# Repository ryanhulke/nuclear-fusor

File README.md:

# Nuclear Fusor
A [nuclear fusor](https://en.wikipedia.org/wiki/Fusor) is an inertial electrostatic confinement device that uses a strong electric field to ionize deuterium gas and accelerate the ions toward the center of a vacuum chamber. This is accomplished by applying a large negative voltage to an inner metal grid (the cathode) relative to the grounded chamber wall (the anode). The chamber is operated at low pressure so that ions can travel significant distances and gain energy from the electric field before colliding with other particles. Near the center of the device, some ions collide with enough kinetic energy that, although they still cannot classically overcome the strong [Coulomb repulsion force](https://en.wikipedia.org/wiki/Coulomb's_law) between their positively charged nuclei, they can occasionally [tunnel](https://en.wikipedia.org/wiki/Quantum_tunnelling) through the Coulomb barrier and may fuse, releasing energy and producing fusion products such as neutrons. These devices are purely experimental; they are highly energy-inefficient and have no commercial future. If you have to ask, "then why would I build one?", you probably shouldn't.

## Project Description
Hardware, firmware, and desktop software for the fusor. The build employs 3 microcontrollers with Bluetooth Low-Energy (BLE). One interfaces with the pressure gauge and streams pressure readings to the control panel, another monitors the high-voltage and current, and the third actuates the gas metering valve for remote pressure control. The desktop app control panel brings the live readouts and valve controls together, with option to stream your phone camera to your computer so you can view the plasma at a safe distance. You can also replay recorded sensor logs and camera footage in the control panel for post-run analysis, in either standard or mobile view.

## Core Components
- a vacuum pump
  - https://www.amazon.com/Kozyvacu-Dual-Stage-HVAC-Vacuum-Pump/dp/B01N0SYCL4/ref=sr_1_1?sr=8-1
- a vacuum chamber with a view port
  - source these parts from ebay. Use KF or Conflat fittings.
- a high-voltage feedthrough into the chamber
- an inner grid connected to the feedthrough (ex. protein shaker ball)
- a variable power supply capable of at least -20kV at a few mA
- deuterium gas source (or just air for testing)
- MKS 901P pressure gauge
- pressure gauge readout board ([pressure-gauge-readout\hardware](pressure-gauge-readout/hardware))
-  remote-controlled valve ([valve-control/Parts.md](valve-control/Parts.md))
- ammeter/voltmeter readout board ([meter-readouts\hardware](meter-readouts/hardware))
- NEMA 17 Stepper motor (mounted to a needle valve on the deuterium inlet side) and driver
- (optional) ESP32-C6 microcontroller to control the motor
  - a more efficient design would be to incorporate valve control into the meter readout board's PCB

## Repository Layout

| Path | Purpose |
| --- | --- |
| `control-panel/` | Windows OpenGL control panel for pressure, meter, valve control, sensor logging, camera background, and playback. |
| `meter-readouts/` | ESP32-C6 firmware and KiCad hardware for the high-voltage/current readout board. |
| `pressure-gauge-readout/` | ESP32-S3 firmware, desktop utilities, and KiCad hardware for the MKS 901P pressure gauge BLE bridge. |
| `valve-control/` | ESP32-C6 firmware for the stepper-driven valve controller. |
| `docs/` | Project notes and supporting documentation. |

Generated build outputs, local logs, camera media, reference papers, IDE state, and local tool installs are intentionally ignored.

## Getting Started
First, check out the hardware and parts lists to make sure you have what you need. Then, set up the software toolchain(s) for the components you want to build.

| What | Toolchain | Where to start |
| --- | --- | --- |
| **Control panel** — the Windows desktop app | CMake + Visual Studio C++ build tools + OpenCV | [control-panel/README.md](control-panel/README.md) |
| **Firmware** — the three microcontroller boards | PlatformIO | [Firmware](#firmware) below |

Everything below assumes **PowerShell, run from the repo root**. Both toolchains need:

- Windows 10 or newer
- Git (`git --version` to confirm)

### Control Panel

The control panel is a native OpenGL desktop app for the live readouts, valve control, camera, sensor logging, and playback. Its setup has a few steps that are easy to get wrong (installing the C++ build tools, pointing CMake at OpenCV, and adding OpenCV's DLLs to `PATH` before running), so it is documented in one place rather than split across files:

**Follow [control-panel/README.md](control-panel/README.md) top to bottom.** It takes you through installing the build tools, installing OpenCV, building, and running, in order.

### Firmware

The firmware runs on three Seeed XIAO microcontrollers that talk to the control panel over BLE.

**1. Install the toolchain**

- **Python 3** — install from https://www.python.org/ with "Add Python to PATH" checked.
- **PlatformIO Core** — install with pip, then confirm it is on `PATH`:
  ```powershell
  pip install platformio
  pio --version
  ```
- **USB drivers for the Seeed XIAO boards** — usually automatic on Windows 10+. Install a driver manually only if a plugged-in board never shows up.

**2. Build and flash each board**

Each board is built from its own directory. The three commands are the same every time: `pio run` compiles, `pio run -t upload` flashes the board over USB, and `pio device monitor` opens the serial console.

```powershell
cd meter-readouts\firmware
pio run
pio run -t upload
pio device monitor

cd ..\..\pressure-gauge-readout\firmware
pio run
pio run -t upload
pio device monitor

cd ..\..\valve-control\firmware
pio run
pio run -t upload
pio device monitor
```

**3. Reference**

Per-board behavior and BLE payloads are documented in:

- [meter-readouts/firmware/README.md](meter-readouts/firmware/README.md)
- [pressure-gauge-readout/README.md](pressure-gauge-readout/README.md) and [pressure-gauge-readout/firmware/README.md](pressure-gauge-readout/firmware/README.md)
- [valve-control/firmware/README.md](valve-control/firmware/README.md)

## BLE Devices

| Device | BLE name | Role |
| --- | --- | --- |
| Meter readout | `Fusor-Meter` | Publishes filtered high-voltage/current readings as `kv=<n>,ma=<n>,sat=<bits>`. |
| Pressure gauge | `PG-XIAO` | Publishes the MKS 901P pressure readout as text. |
| Valve control | `Fusor-Valve` | Publishes `pos=<n>,open=<n>,mode=<mode>` and accepts movement commands. |

The control panel discovers these devices automatically by BLE name/service UUID.

## Hardware

KiCad projects are included for the readout boards:

- `meter-readouts/hardware/MeterReadouts.kicad_pro`
- `pressure-gauge-readout/hardware/readoutPCB.kicad_pro`

## License
MIT.

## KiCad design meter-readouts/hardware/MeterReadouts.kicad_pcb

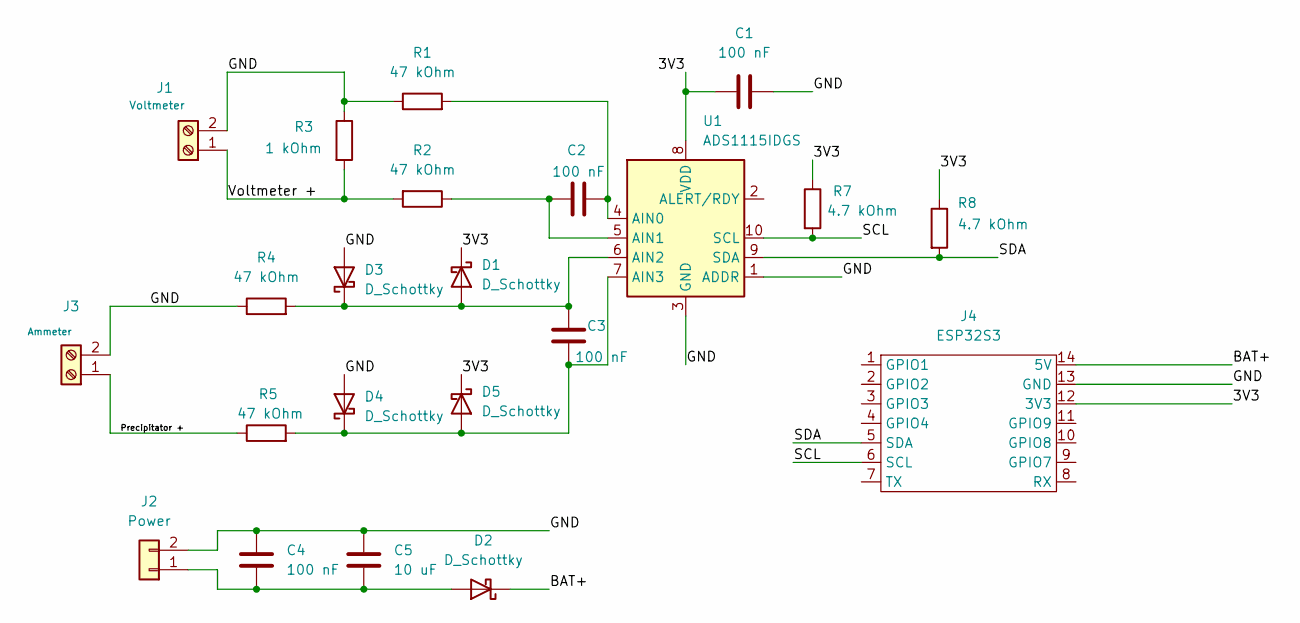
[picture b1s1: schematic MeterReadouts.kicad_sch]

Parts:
C1, C2, C3, C4: 100 nF; C_0805_2012Metric
C5: 10 uF; C_0805_2012Metric
D1, D2, D3, D4, D5: D_Schottky; D_SOD-123
J1: Voltmeter; TerminalBlock_Phoenix_MKDS-1,5-2-5.08_1x02_P5.08mm_Horizont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
J2: Power; TerminalBlock_Phoenix_MKDS-1,5-2-5.08_1x02_P5.08mm_Horizont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
J3: Ammeter; TerminalBlock_Phoenix_MKDS-1,5-2-5.08_1x02_P5.08mm_Horizont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
J4: ESP32S3; XIAO-ESP32S3-DIP
R1, R2, R4, R5: 47 kOhm; R_0805_2012Metric
R3: 1 kOhm; R_0805_2012Metric
R7, R8: 4.7 kOhm; R_0805_2012Metric
U1: ADS1115IDGS; TSSOP-10_3x3mm_P0.5mm

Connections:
/3V3: C1.1, D1.1 (K), D5.1 (K), J4.12 (3V3), R7.1, R8.1, U1.8 (VDD)
/<NO NET>: J1.1, R2.2, R3.2
/BAT+: D2.1 (K), J4.14 (5V)
/GND: C1.2, C4.2, C5.2, D3.2 (A), D4.2 (A), J1.2, J2.2, J3.2, J4.13 (GND), R1.1, R3.1, R4.1, U1.1 (ADDR), U1.3 (GND)
/Precipitator +: J3.1, R5.1
/SCL: J4.6 (SCL), R7.2, U1.10 (SCL)
/SDA: J4.5 (SDA), R8.2, U1.9 (SDA)
unnamed: C3.2, D1.2 (A), D3.1 (K), R4.2, U1.6 (AIN2)
unnamed: C4.1, C5.1, D2.2 (A), J2.1
unnamed: C3.1, D4.1 (K), D5.2 (A), R5.2, U1.7 (AIN3)
unnamed: C2.2, R1.2, U1.4 (AIN0)
unnamed: C2.1, R2.1, U1.5 (AIN1)

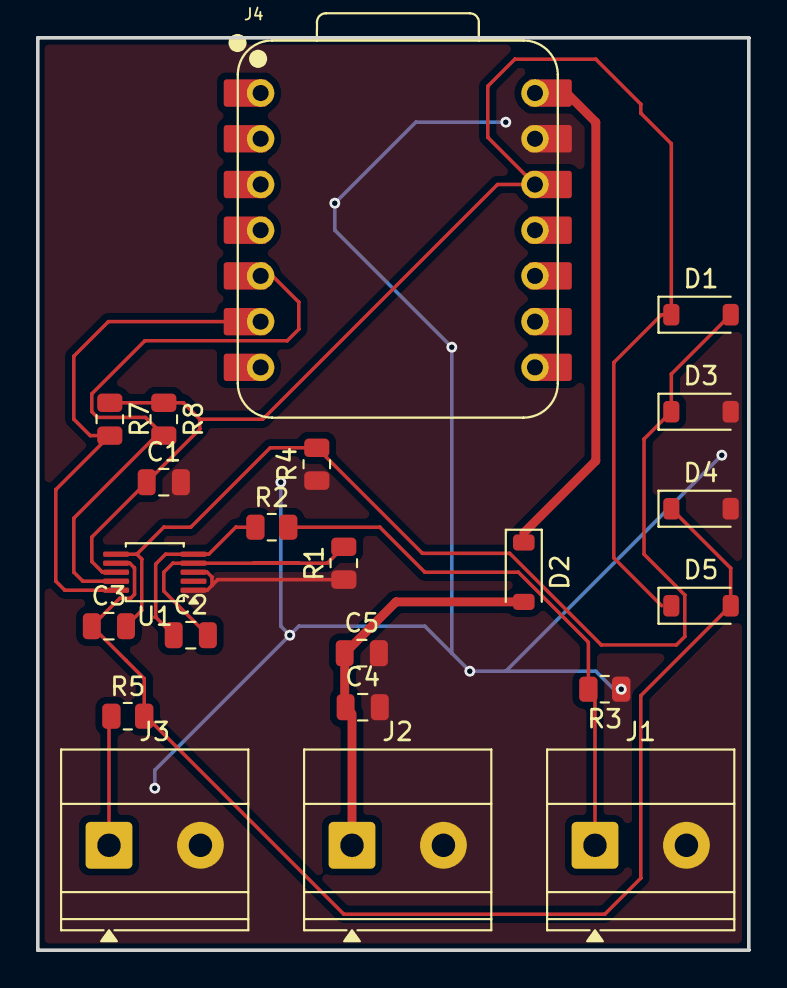
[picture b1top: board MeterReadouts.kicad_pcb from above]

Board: 2 copper layers, 39.5 x 50.7 mm, 22 parts (0 on the bottom side), 12 nets.

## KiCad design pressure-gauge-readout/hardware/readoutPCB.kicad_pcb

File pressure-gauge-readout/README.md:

# Pressure Gauge Readout

BLE bridge, desktop utilities, and hardware files for reading an MKS 901P
pressure transducer from the control panel app.

## Layout

| Path | Purpose |
| --- | --- |
| `firmware/` | PlatformIO firmware for the Seeed XIAO ESP32S3 BLE pressure bridge. |
| `desktop/server.py` | Simple BLE smoke-test listener for the production pressure payload. |
| `desktop/calibrate_901p.py` | Maintenance script for 901P command/calibration workflows. |
| `hardware/` | KiCad PCB project and mechanical files. |
| `docs/901P-Loadlock-Transducer-Manual.pdf` | Local copy of the 901P transducer manual. |

## Firmware

The firmware uses PlatformIO. If PlatformIO is not installed yet:

```powershell
python -m pip install --upgrade platformio
pio --version
```

Build and upload from the firmware directory:

```powershell
cd pressure-gauge-readout\firmware
pio run
pio run -t upload
```

The production firmware advertises as `PG-XIAO`, queries `@253PR4?;FF`, and
publishes the parsed pressure string over BLE. See `firmware/README.md` for the
full BLE UUIDs and payload format.

## BLE Smoke Test

Use `desktop/server.py` when you only need to verify that the board advertises,
connects, and publishes pressure notifications.

Install the Python dependency for the desktop scripts:

```powershell
python -m pip install bleak
```

Run from the repo root:

```powershell
python pressure-gauge-readout\desktop\server.py
```

The script prints each BLE notification as raw text. It is intentionally small
and does not depend on the control panel app.

## Calibration Utility

`desktop/calibrate_901p.py` is kept as a maintenance utility for direct 901P
command/calibration workflows. It is not required for normal control panel operation.

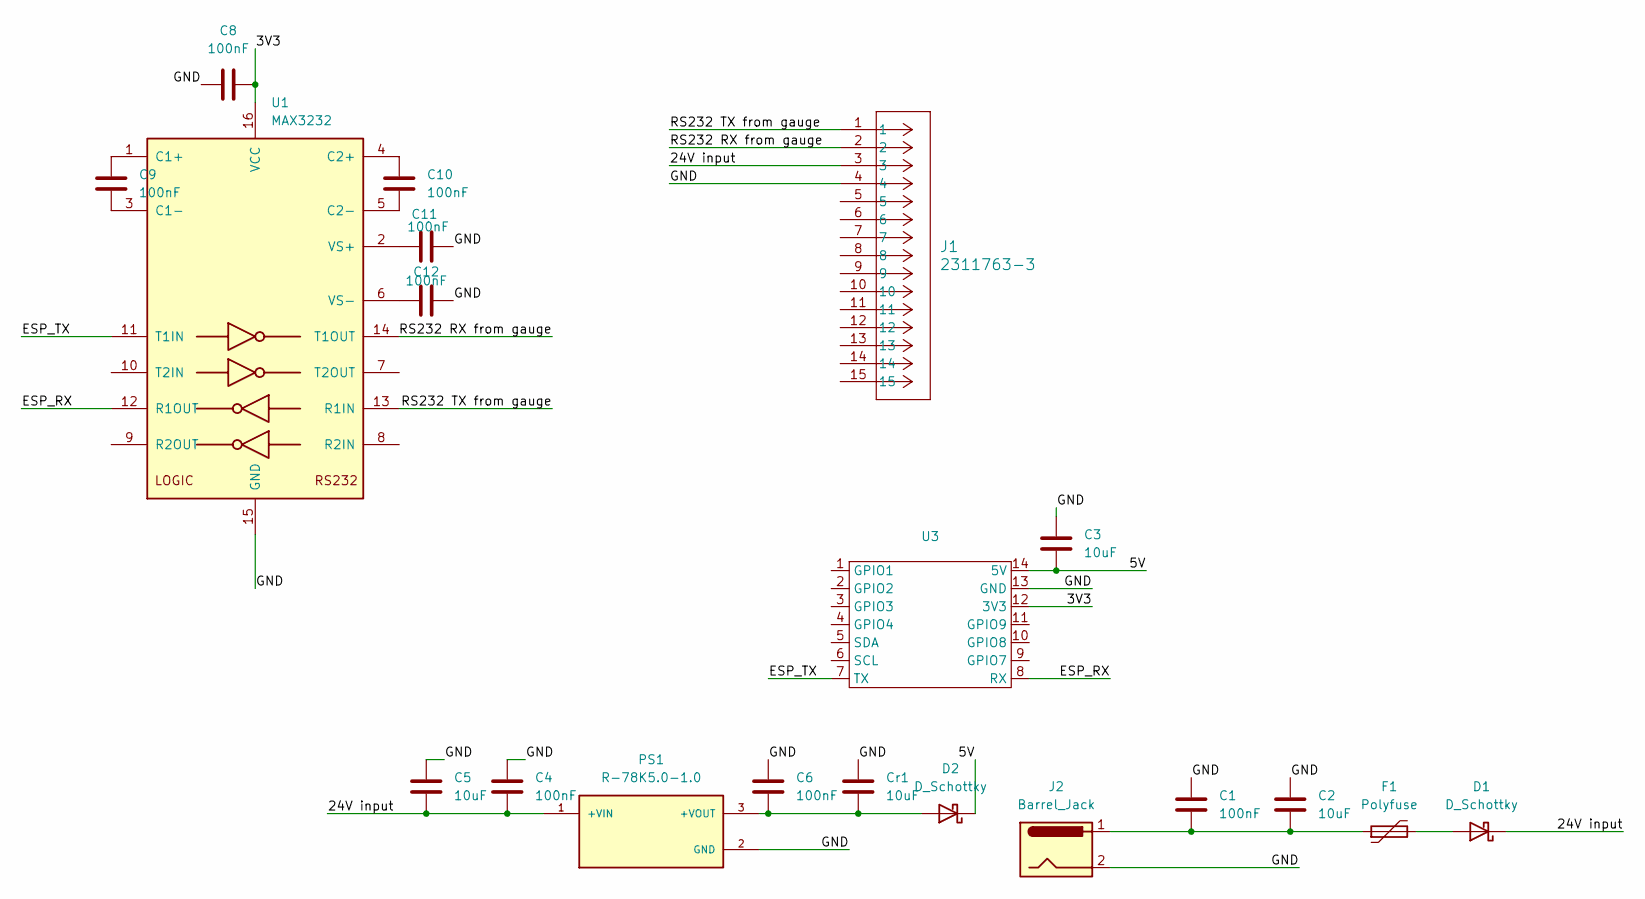
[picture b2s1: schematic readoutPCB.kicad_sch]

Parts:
C1, C4, C6, C8, C9, C10, C11, C12: 100nF; C_0603_1608Metric
C2, C3, C5: 10uF; C_0603_1608Metric
Cr1: 10uF; C_0603_1608Metric
D1, D2: D_Schottky; D_SOD-123
F1: Polyfuse; Fuse_1812_4532Metric
J1: 2311763-3; CONN_2311763-3_TEC
J2: Barrel_Jack; BarrelJack_CUI_PJ-102AH_Horizontal
PS1: R-78K5.0-1.0; CONV_R-78K5.0-1.0; PARTREV 0/2023
U1: MAX3232; SOIC-16_3.9x9.9mm_P1.27mm
U3: XIAO-ESP32S3-DIP

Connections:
/3V3: C8.2, U1.16 (VCC), U3.12 (3V3)
/5V: C3.2, D2.1 (K), U3.14 (5V)
/24V input: C4.2, C5.2, D1.1 (K), J1.3, PS1.1 (+VIN)
/ESP_RX: U1.12 (R1OUT), U3.8 (RX)
/ESP_TX: U1.11 (T1IN), U3.7 (TX)
/GND: C1.1, C2.1, C3.1, C4.1, C5.1, C6.1, C8.1, C11.2, C12.2, Cr1.1, J1.4, J2.2, PS1.2 (GND), U1.15 (GND), U3.13 (GND)
/RS232 RX from gauge: J1.2, U1.14 (T1OUT)
/RS232 TX from gauge: J1.1, U1.13 (R1IN)
unnamed: C1.2, C2.2, F1.1, J2.1
unnamed: D1.2 (A), F1.2
unnamed: C6.2, Cr1.2, D2.2 (A), PS1.3 (+VOUT)
unnamed: C9.2, U1.1 (C1+)
unnamed: C9.1, U1.3 (C1-)
unnamed: C10.2, U1.4 (C2+)
unnamed: C10.1, U1.5 (C2-)
unnamed: C11.1, U1.2 (VS+)
unnamed: C12.1, U1.6 (VS-)

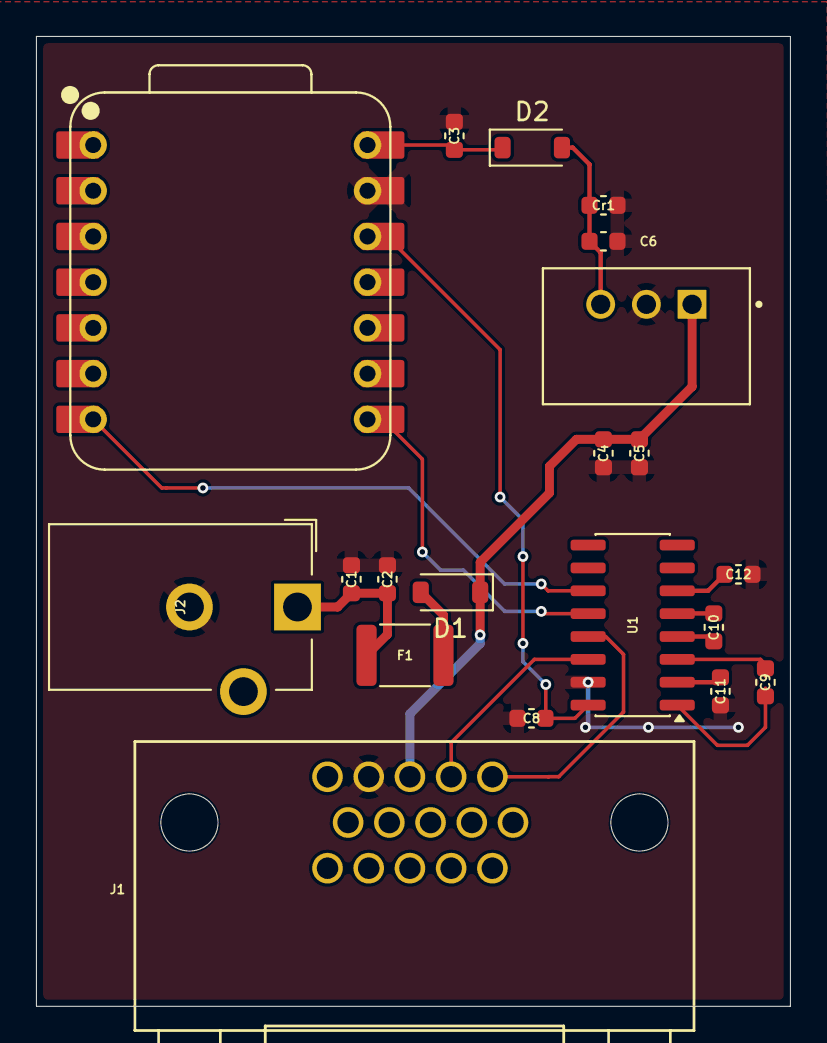
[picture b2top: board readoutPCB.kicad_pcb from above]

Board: 2 copper layers, 41.9 x 53.9 mm, 20 parts (0 on the bottom side), 17 nets.

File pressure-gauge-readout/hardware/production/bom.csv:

Designator,Footprint,Quantity,Value,LCSC Part #
"C1, C10, C11, C12, C4, C6, C8, C9",0603,8,100nF,
"C2, C3, C5, CR1",0603,4,10uF,
"D1, D2",D_SOD-123,2,D_Schottky,
F1,1812,1,Polyfuse,
U1,SOIC-16_3.9x9.9mm_P1.27mm,1,MAX3232,

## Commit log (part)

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2026-06-07 init
2026-06-10 readme
    Added a project description section detailing hardware and software components, including microcontroller functions and app features. Corrected links in the core components list.
2026-06-10 Fix formatting in README.md introduction
2026-06-10 readme
